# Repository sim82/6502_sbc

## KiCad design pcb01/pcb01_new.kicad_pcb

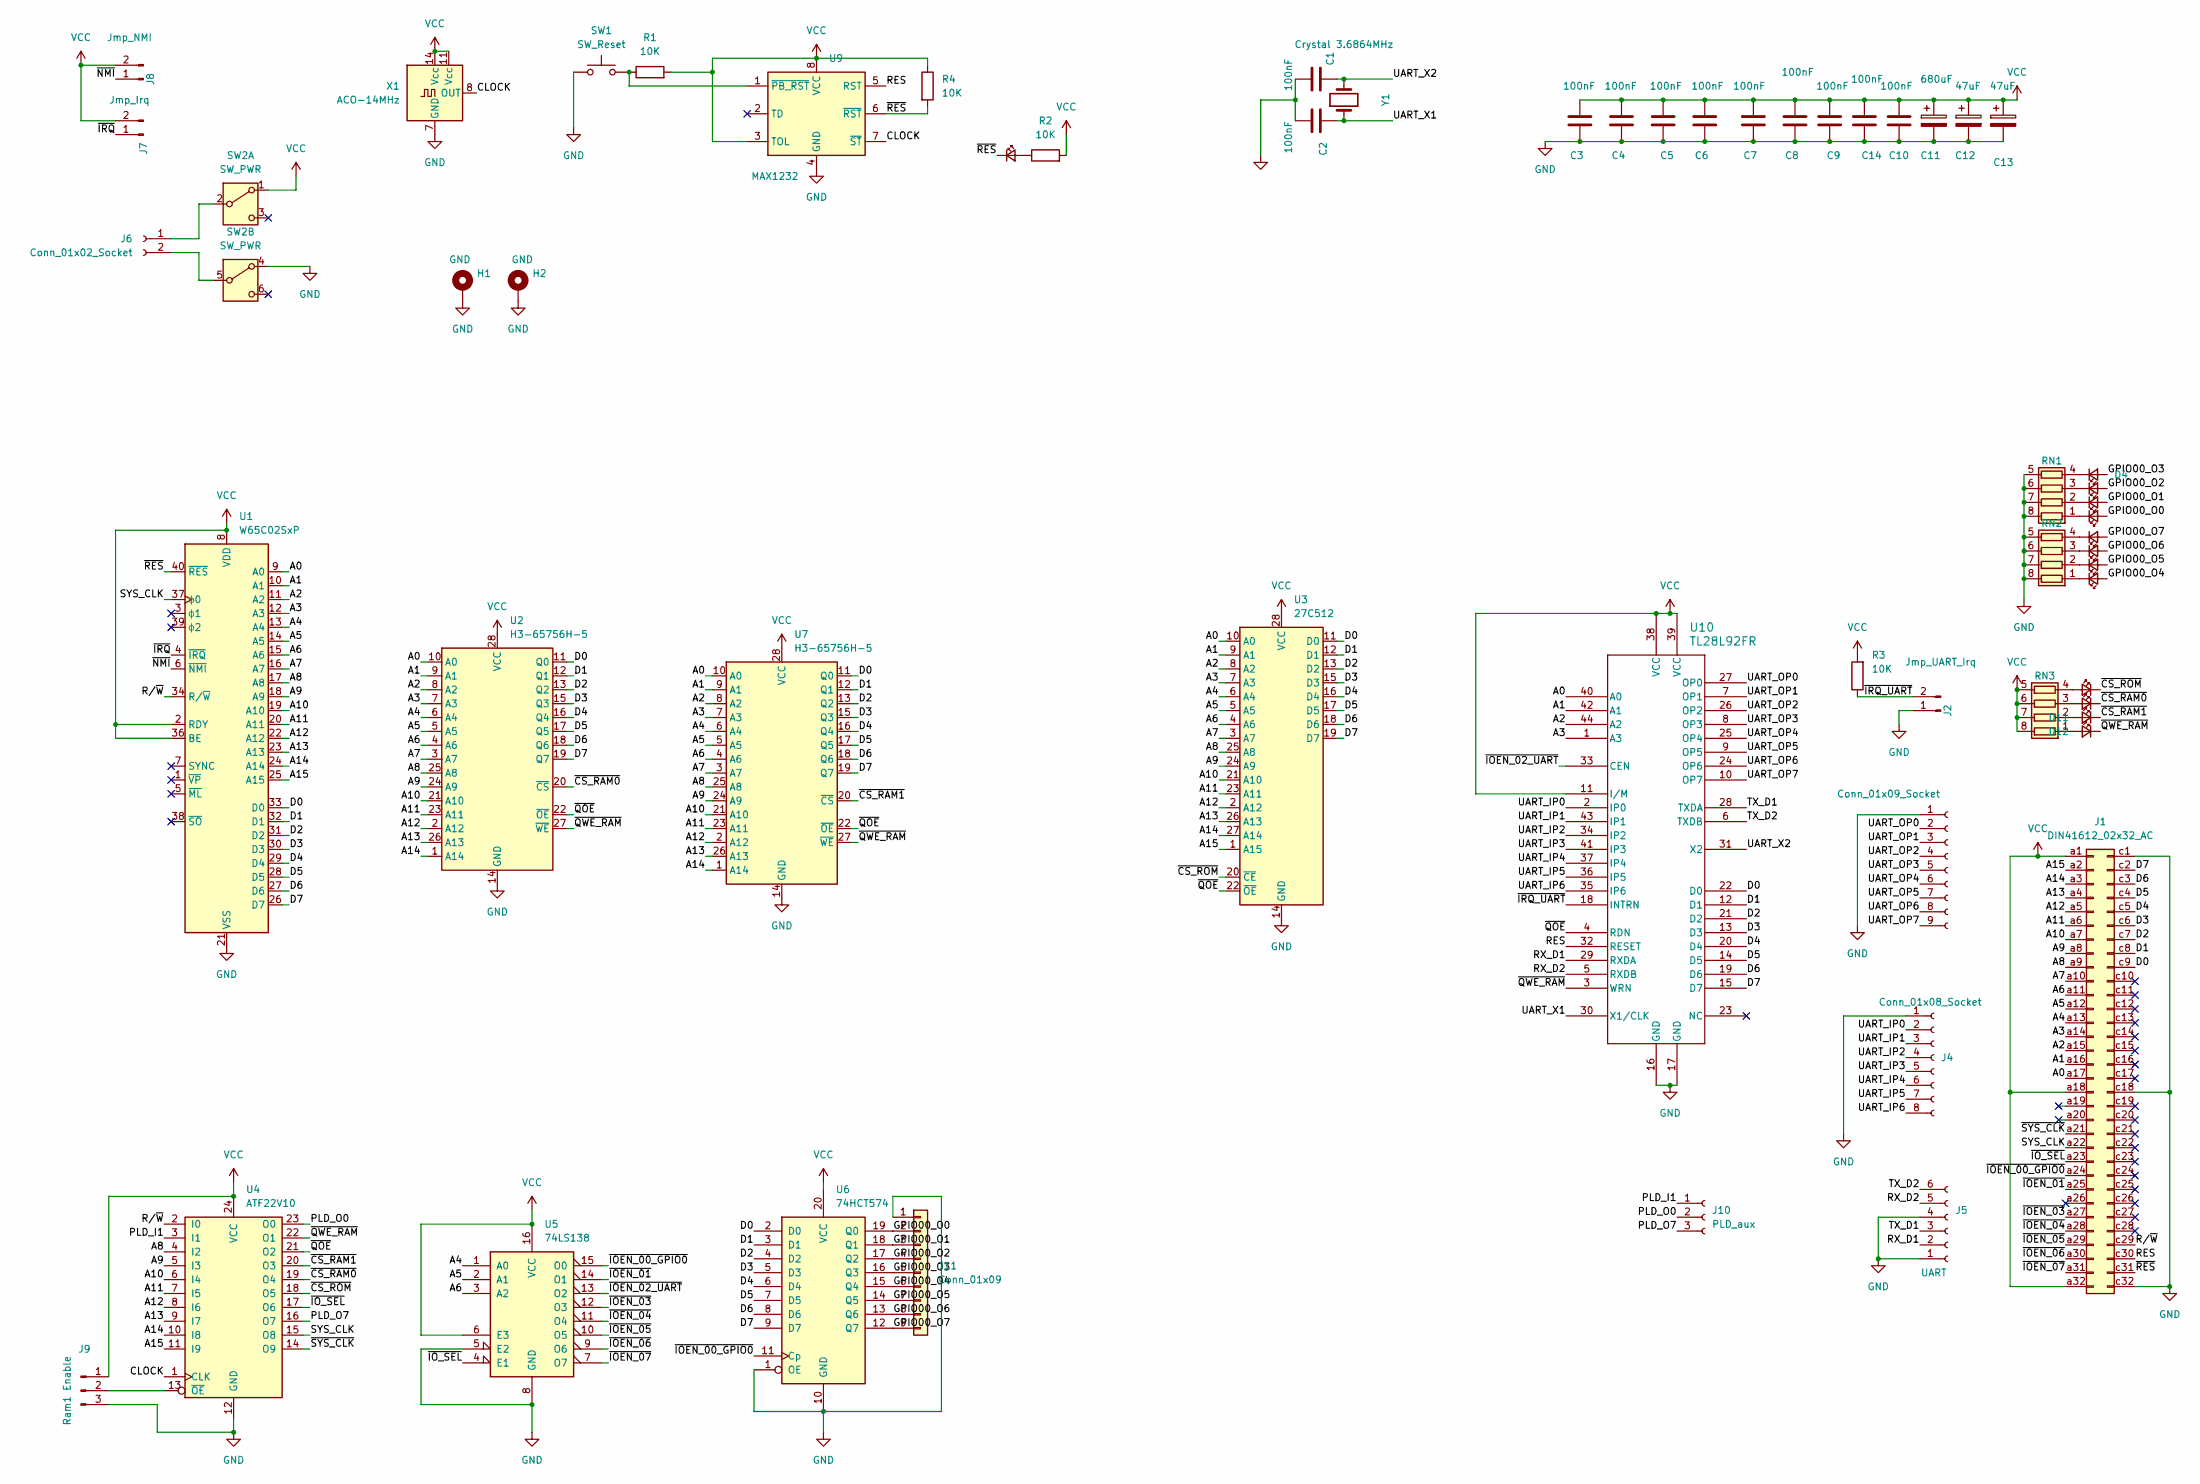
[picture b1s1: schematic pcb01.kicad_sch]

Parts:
C1, C2: 100nF; C_Disc_D4.7mm_W2.5mm_P5.00mm
C3, C4, C5, C6, C7, C8, C9, C10, C14: 100nF; C_0805_2012Metric_Pad1.18x1.45mm_HandSolder
C11: 680uF; CP_Radial_D8.0mm_P5.00mm
C12, C13: 47uF; CP_Radial_D4.0mm_P2.00mm
D1, D2, D3, D4, D5, D6, D7, D8, D9, D10, D11, D12, D13: LED_Small; LED_0805_2012Metric_Pad1.15x1.40mm_HandSolder
H1, H2: GND; MountingHole_3.2mm_M3_DIN965_Pad
J1: DIN41612_02x32_AC; DIN41612_C_2x32_Male_Horizontal_THT
J2: Jmp_UART_Irq; PinSocket_1x02_P2.54mm_Vertical
J3: Conn_01x09_Socket; PinSocket_1x09_P2.54mm_Vertical
J4: Conn_01x08_Socket; PinSocket_1x08_P2.54mm_Vertical
J5: UART; PinSocket_1x06_P2.54mm_Vertical
J6: Conn_01x02_Socket; PinSocket_1x02_P2.54mm_Vertical
J7: Jmp_Irq; PinHeader_1x02_P2.54mm_Vertical
J8: Jmp_NMI; PinHeader_1x02_P2.54mm_Vertical
J9: Ram1 Enable; PinHeader_1x03_P2.54mm_Vertical
J10: PLD_aux; PinSocket_1x03_P2.54mm_Vertical
J11: Conn_01x09; PinSocket_1x09_P2.54mm_Vertical
R1, R2, R3, R4: 10K; R_0805_2012Metric_Pad1.20x1.40mm_HandSolder
RN1, RN2, RN3: R_Pack04; R_Array_Convex_4x0612
SW1: SW_Reset; SW_TH_Tactile_Omron_B3F-10xx
SW2: SW_PWR; 7x7DPDT
U1: W65C02SxP; DIP-40_W15.24mm_Socket
U2, U7: H3-65756H-5; DIP-28_W7.62mm_Socket
U3: 27C512; DIP-28_W15.24mm_Socket
U4: ATF22V10; DIP-24_W7.62mm_Socket
U5: 74LS138; DIP-16_W7.62mm_Socket
U6: 74HCT574; DIP-20_W7.62mm_Socket
U9: MAX1232; SO-8_3.9x4.9mm_P1.27mm
U10: TL28L92FR; MQFP-44_10x10mm_P0.8mm
X1: ACO-14MHz; DIP-14_W7.62mm
Y1: Crystal 3.6864MHz; Crystal_HC49-4H_Vertical

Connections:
/A0: J1.a17, U1.9 (A0), U2.10 (A0), U3.10 (A0), U7.10 (A0), U10.40 (A0)
/A1: J1.a16, U1.10 (A1), U2.9 (A1), U3.9 (A1), U7.9 (A1), U10.42 (A1)
/A2: J1.a15, U1.11 (A2), U2.8 (A2), U3.8 (A2), U7.8 (A2), U10.44 (A2)
/A3: J1.a14, U1.12 (A3), U2.7 (A3), U3.7 (A3), U7.7 (A3), U10.1 (A3)
/A4: J1.a13, U1.13 (A4), U2.6 (A4), U3.6 (A4), U5.1 (A0), U7.6 (A4)
/A5: J1.a12, U1.14 (A5), U2.5 (A5), U3.5 (A5), U5.2 (A1), U7.5 (A5)
/A6: J1.a11, U1.15 (A6), U2.4 (A6), U3.4 (A6), U5.3 (A2), U7.4 (A6)
/A7: J1.a10, U1.16 (A7), U2.3 (A7), U3.3 (A7), U7.3 (A7)
/A8: J1.a9, U1.17 (A8), U2.25 (A8), U3.25 (A8), U4.4 (I2), U7.25 (A8)
/A9: J1.a8, U1.18 (A9), U2.24 (A9), U3.24 (A9), U4.5 (I3), U7.24 (A9)
/A10: J1.a7, U1.19 (A10), U2.21 (A10), U3.21 (A10), U4.6 (I4), U7.21 (A10)
/A11: J1.a6, U1.20 (A11), U2.23 (A11), U3.23 (A11), U4.7 (I5), U7.23 (A11)
/A12: J1.a5, U1.22 (A12), U2.2 (A12), U3.2 (A12), U4.8 (I6), U7.2 (A12)
/A13: J1.a4, U1.23 (A13), U2.26 (A13), U3.26 (A13), U4.9 (I7), U7.26 (A13)
/A14: J1.a3, U1.24 (A14), U2.1 (A14), U3.27 (A14), U4.10 (I8), U7.1 (A14)
/A15: J1.a2, U1.25 (A15), U3.1 (A15), U4.11 (I9)
/CLOCK: U4.1 (CLK), U9.7 (~ST), X1.8 (OUT)
/D0: J1.c9, U1.33 (D0), U2.11 (Q0), U3.11 (D0), U6.2 (D0), U7.11 (Q0), U10.22 (D0)
/D1: J1.c8, U1.32 (D1), U2.12 (Q1), U3.12 (D1), U6.3 (D1), U7.12 (Q1), U10.12 (D1)
/D2: J1.c7, U1.31 (D2), U2.13 (Q2), U3.13 (D2), U6.4 (D2), U7.13 (Q2), U10.21 (D2)
/D3: J1.c6, U1.30 (D3), U2.15 (Q3), U3.15 (D3), U6.5 (D3), U7.15 (Q3), U10.13 (D3)
/D4: J1.c5, U1.29 (D4), U2.16 (Q4), U3.16 (D4), U6.6 (D4), U7.16 (Q4), U10.20 (D4)
/D5: J1.c4, U1.28 (D5), U2.17 (Q5), U3.17 (D5), U6.7 (D5), U7.17 (Q5), U10.14 (D5)
/D6: J1.c3, U1.27 (D6), U2.18 (Q6), U3.18 (D6), U6.8 (D6), U7.18 (Q6), U10.19 (D6)
/D7: J1.c2, U1.26 (D7), U2.19 (Q7), U3.19 (D7), U6.9 (D7), U7.19 (Q7), U10.15 (D7)
/GPIO00_O0: D1.2 (A), J11.2, U6.19 (Q0)
/GPIO00_O1: D2.2 (A), J11.3, U6.18 (Q1)
/GPIO00_O2: D3.2 (A), J11.4, U6.17 (Q2)
/GPIO00_O3: D4.2 (A), J11.5, U6.16 (Q3)
/GPIO00_O4: D5.2 (A), J11.6, U6.15 (Q4)
/GPIO00_O5: D6.2 (A), J11.7, U6.14 (Q5)
/GPIO00_O6: D7.2 (A), J11.8, U6.13 (Q6)
/GPIO00_O7: D8.2 (A), J11.9, U6.12 (Q7)
/PLD_I1: J10.1, U4.3 (I1)
/PLD_O0: J10.2, U4.23 (O0)
/PLD_O7: J10.3, U4.16 (O7)
/RES: J1.c30, U9.5 (RST), U10.32 (RESET)
/RX_D1: J5.2, U10.29 (RXDA)
/RX_D2: J5.5, U10.5 (RXDB)
/R/~W: J1.c29, U1.34 (R/~W), U4.2 (I0)
/SYS_CLK: J1.a22, U1.37 (ϕ0), U4.15 (O8)
/TX_D1: J5.3, U10.28 (TXDA)
/TX_D2: J5.6, U10.6 (TXDB)
/UART_IP0: J4.2, U10.2 (IP0)
/UART_IP1: J4.3, U10.43 (IP1)
/UART_IP2: J4.4, U10.34 (IP2)
/UART_IP3: J4.5, U10.41 (IP3)
/UART_IP4: J4.6, U10.37 (IP4)
/UART_IP5: J4.7, U10.36 (IP5)
/UART_IP6: J4.8, U10.35 (IP6)
/UART_OP0: J3.2, U10.27 (OP0)
/UART_OP1: J3.3, U10.7 (OP1)
/UART_OP2: J3.4, U10.26 (OP2)
/UART_OP3: J3.5, U10.8 (OP3)
/UART_OP4: J3.6, U10.25 (OP4)
/UART_OP5: J3.7, U10.9 (OP5)
/UART_OP6: J3.8, U10.24 (OP6)
/UART_OP7: J3.9, U10.10 (OP7)
/UART_X1: C2.1, U10.30 (X1/CLK), Y1.1
/UART_X2: C1.1, U10.31 (X2), Y1.2
/~CS_RAM0: D10.1 (K), U2.20 (~CS), U4.19 (O4)
/~CS_RAM1: D11.1 (K), U4.20 (O3), U7.20 (~CS)
/~CS_ROM: D9.1 (K), U3.20 (~CE), U4.18 (O5)
/~IOEN_00_GPIO0: J1.a24, U5.15 (O0), U6.11 (Cp)
/~IOEN_01: J1.a25, U5.14 (O1)
/~IOEN_02_UART: U5.13 (O2), U10.33 (CEN)
/~IOEN_03: J1.a27, U5.12 (O3)
/~IOEN_04: J1.a28, U5.11 (O4)
/~IOEN_05: J1.a29, U5.10 (O5)
/~IOEN_06: J1.a30, U5.9 (O6)
/~IOEN_07: J1.a31, U5.7 (O7)
/~IO_SEL: J1.a23, U4.17 (O6), U5.4 (E1)
/~IRQ_UART: J2.2, R3.1, U10.18 (INTRN)
/~IRQ: J7.1, U1.4 (~IRQ)
/~NMI: J8.1, U1.6 (~NMI)
/~QOE: U2.22 (~OE), U3.22 (~OE), U4.21 (O2), U7.22 (~OE), U10.4 (RDN)
/~QWE_RAM: D12.1 (K), U2.27 (~WE), U4.22 (O1), U7.27 (~WE), U10.3 (WRN)
/~RES: D13.1 (K), J1.c31, R4.2, U1.40 (~RES), U9.6 (~RST)
/~SYS_CLK: J1.a21, U4.14 (O9)
GND: C1.2, C2.2, C3.2, C4.2, C5.2, C6.2, C7.2, C8.2, C9.2, C10.2, C11.2, C12.2, C13.2, C14.2, H1.1, H2.1, J1.c1, J1.c18, J1.c32, J2.1, J3.1, J4.1, J5.1, J5.4, J9.3, J11.1, RN1.5 (R4.2), RN1.6 (R3.2), RN1.7 (R2.2), RN1.8 (R1.2), RN2.5 (R4.2), RN2.6 (R3.2), RN2.7 (R2.2), RN2.8 (R1.2), SW1.2, SW2.4 (A), U1.21 (VSS), U2.14 (GND), U3.14 (GND), U4.12 (GND), U5.5 (E2), U5.8 (GND), U6.1 (OE), U6.10 (GND), U7.14 (GND), U9.4 (GND), U10.16 (GND), U10.17 (GND), X1.7 (GND)
unnamed: D1.1 (K), RN1.1 (R1.1)
unnamed: D2.1 (K), RN1.2 (R2.1)
unnamed: D3.1 (K), RN1.3 (R3.1)
unnamed: D4.1 (K), RN1.4 (R4.1)
unnamed: D5.1 (K), RN2.1 (R1.1)
unnamed: D6.1 (K), RN2.2 (R2.1)
unnamed: D7.1 (K), RN2.3 (R3.1)
unnamed: D8.1 (K), RN2.4 (R4.1)
unnamed: D9.2 (A), RN3.4 (R4.1)
unnamed: D10.2 (A), RN3.3 (R3.1)
unnamed: D11.2 (A), RN3.2 (R2.1)
unnamed: D12.2 (A), RN3.1 (R1.1)
unnamed: D13.2 (A), R2.1
unnamed: J6.1, SW2.2 (B)
unnamed: J6.2, SW2.5 (B)
unnamed: J9.2, U4.13 (~OE)
unnamed: R1.1, SW1.1, U9.1 (~PB_RST)
VCC: C3.1, C4.1, C5.1, C6.1, C7.1, C8.1, C9.1, C10.1, C11.1, C12.1, C13.1, C14.1, J1.a1, J1.a18, J1.a32, J7.2, J8.2, J9.1, R1.2, R2.2, R3.2, R4.1, RN3.5 (R4.2), RN3.6 (R3.2), RN3.7 (R2.2), RN3.8 (R1.2), SW2.1 (A), U1.2 (RDY), U1.8 (VDD), U1.36 (BE), U2.28 (VCC), U3.28 (VCC), U4.24 (VCC), U5.6 (E3), U5.16 (VCC), U6.20 (VCC), U7.28 (VCC), U9.3 (TOL), U9.8 (VCC), U10.11 (I/M), U10.38 (VCC), U10.39 (VCC), X1.11 (Vcc), X1.14 (Vcc)

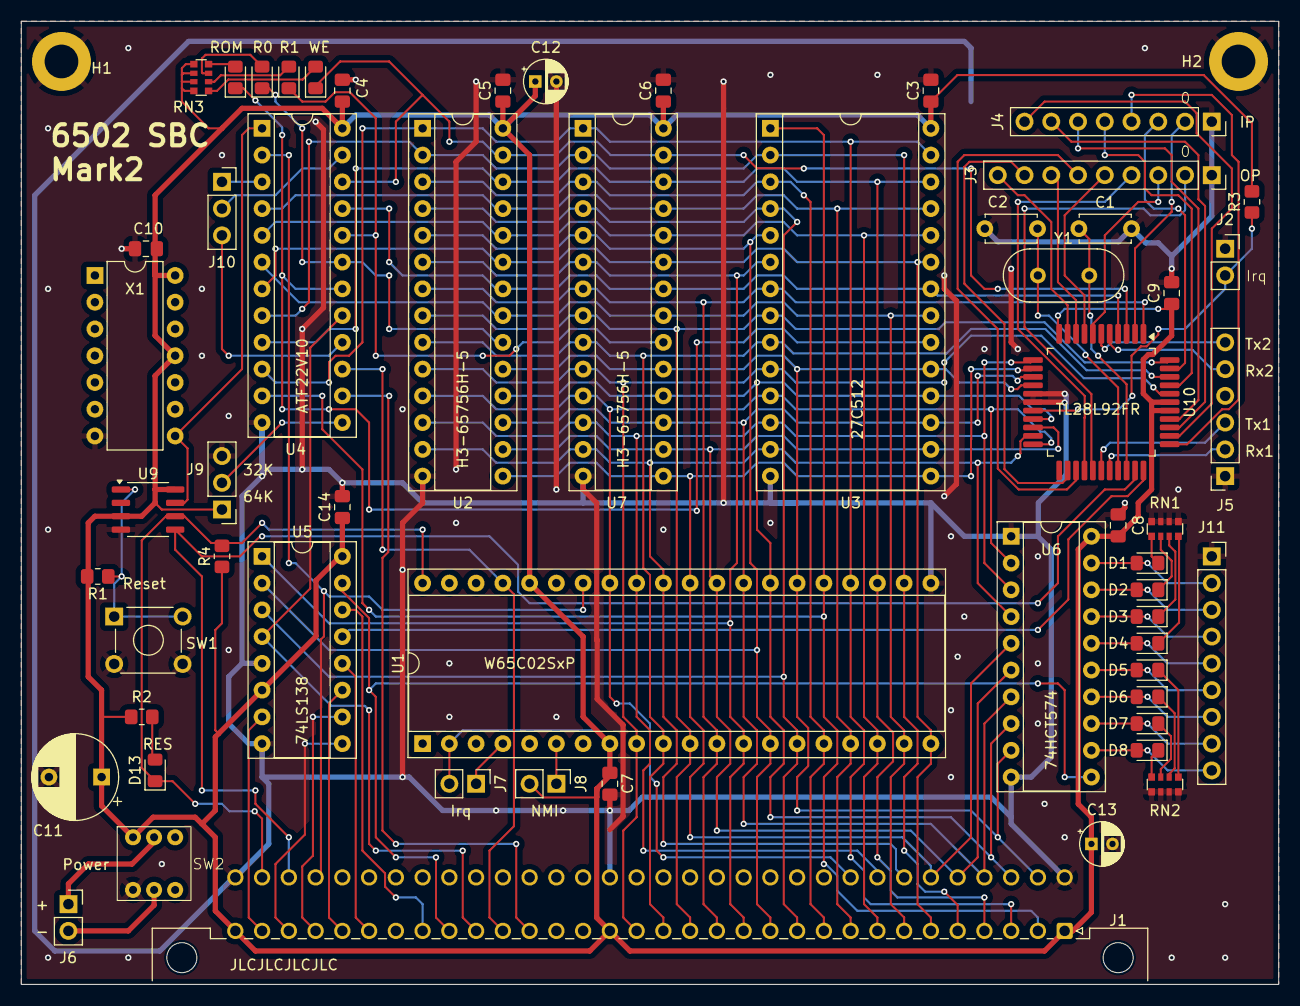
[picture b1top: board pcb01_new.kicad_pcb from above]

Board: 2 copper layers, 119.4 x 91.4 mm, 60 parts (0 on the bottom side), 98 nets.
